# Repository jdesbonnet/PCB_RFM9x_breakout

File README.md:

# RFM9x radio module breakout board

This PCB allows an RFM9x (RFM95, RFM96, RFM97, RFM98) modules to be mounted on
a breadboard. 

I've rotated the RFM module 90 degrees to keep the width as small as possible. 
The width separating the pin headers is 0.8 inches (20.32mm) which is narrow 
enough to have at least one available contact  point on each side.

As of 2018-04-18 this has been submitted for fabrication. I'll update this
note when the board arrives and the design has been verified. 

Arrived 2018-05-03. Tested 2018-05-08. Works, only problem is the tiny font
of the pin labels. Increased font size by 50% (to 0.75mm) and resubmitted as
version 1.0.1.

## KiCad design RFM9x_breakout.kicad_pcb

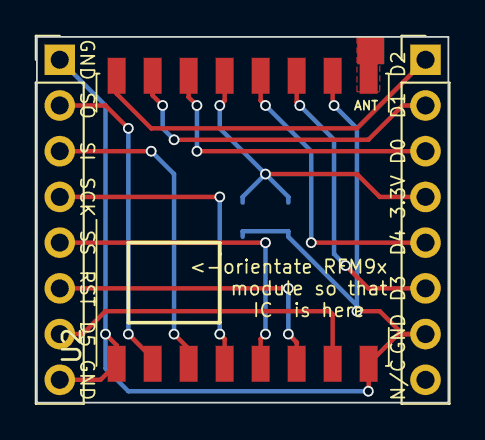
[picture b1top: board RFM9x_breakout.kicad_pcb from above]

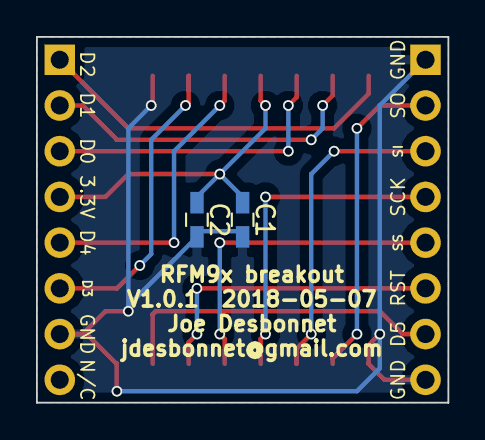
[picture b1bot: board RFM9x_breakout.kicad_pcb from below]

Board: 2 copper layers, 22.9 x 20.3 mm, 5 parts (2 on the bottom side), 13 nets.

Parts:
C1, C2: C; C_0603_HandSoldering
J1, J2: Conn_01x08_Male; Pin_Header_Straight_1x08_Pitch2.54mm
U2: RFM92/95/96/97/98; Hopref_RFM9XW_SMD

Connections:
3.3V: C1.1, C2.1, J2.4, U2.13
GND: C1.2, C2.2, J1.1, J1.8, J2.7, U2.1, U2.8, U2.10
unnamed: J1.2, U2.2
unnamed: J1.3, U2.3
unnamed: J1.4, U2.4
unnamed: J1.5, U2.5
unnamed: J1.6, U2.6
unnamed: J1.7, U2.7
unnamed: J2.1, U2.16
unnamed: J2.2, U2.15
unnamed: J2.3, U2.14
unnamed: J2.5, U2.12
unnamed: J2.6, U2.11

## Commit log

2018-04-15 no comment
2018-04-15 add README
2018-05-07 increase font size of pin labels
